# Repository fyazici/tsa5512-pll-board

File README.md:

# tsa5512-pll-board
PCB for VCO combined with the TV/VCR Tuner controller TSA5512T

VCO is implemented with a simple varactor controlled Colpitts oscillator. 
Capacitor/Inductor values should be adjusted according to the desired operating frequency range. Current component values are chosen to oscillate in FM band.
TSA5512 is a cheap Philips PLL IC mainly made for TV tuner applications. DIY-famous UV916 tuner also contains this chip (like many other tuners).
PLL is configured over I2C, which can easily be achieved with an Arduino board. Programming details can be found in the datasheet (http://pira.cz/pdf/TSA5512.pdf)

Some components are through-hole, because I've had a bunch of them at hand. SMD resistor/capacitors are spread all over the board and they can easily be found on any scrap electronic equipment with a sufficient size.
For higher frequency requirements (UHF band, ~300MHz) original tuner designs can be taken as a reference. BFR92 transistor will be more appropriate for the oscillator and special care should be taken in order to encapsulate the signal nets (t. lines and keepout regions mainly).

3D board view of the top-side:

Note that the gerber outputs are not up-to-date (belongs to an erroneus version). I've laser-printed the board so I did not care about special requirements of any PCB manufacturer. A revisit of layout is required to meet manufacturer demands (some I know of are: OSH Park, Seeedstudio)

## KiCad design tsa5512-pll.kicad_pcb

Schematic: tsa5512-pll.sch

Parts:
C1, C9, C14, C20: 10u; CP_Radial_D8.0mm_P3.80mm
C2, C10: 1u; CP_Radial_D5.0mm_P2.50mm
C3: 39n; C_1206_3216Metric_Pad1.24x1.80mm_HandSolder
C4, C12, C23: 4n7; C_1206_3216Metric_Pad1.24x1.80mm_HandSolder
C5: 180n; C_1206_3216Metric_Pad1.24x1.80mm_HandSolder
C6, C13, C24: 150p; C_1206_3216Metric_Pad1.24x1.80mm_HandSolder
C7, C8: 1n; C_1206_3216Metric_Pad1.24x1.80mm_HandSolder
C11: 27p; C_1206_3216Metric_Pad1.24x1.80mm_HandSolder
C15: 10n; C_1206_3216Metric_Pad1.24x1.80mm_HandSolder
C16, C17: 15p; C_1206_3216Metric_Pad1.24x1.80mm_HandSolder
C18: 330p; C_1206_3216Metric_Pad1.24x1.80mm_HandSolder
C19, C21: 47p; C_1206_3216Metric_Pad1.24x1.80mm_HandSolder
C22: 22p; C_1206_3216Metric_Pad1.24x1.80mm_HandSolder
D1, D2: BB221; D_DO-35_SOD27_P7.62mm_Horizontal
J1, J2, J3: Conn_01x04; PinHeader_1x04_P2.54mm_Vertical
L1: 100n; L_7.3x7.3_H3.5
Q1: BC848W; SOT-323_SC-70_Handsoldering
Q2: BF199; TO-92L_Inline_Wide
R1, R5, R6: 15k; R_1206_3216Metric_Pad1.24x1.80mm_HandSolder
R2, R3, R11: 10k; R_1206_3216Metric_Pad1.24x1.80mm_HandSolder
R4: 22k; R_1206_3216Metric_Pad1.24x1.80mm_HandSolder
R7: 270R; R_1206_3216Metric_Pad1.24x1.80mm_HandSolder
R8: 680R; R_1206_3216Metric_Pad1.24x1.80mm_HandSolder
R9, R10, R12: 4k7; R_1206_3216Metric_Pad1.24x1.80mm_HandSolder
TP1, TP2: Test_Point; TestPoint_Pad_D1.5mm
TP3: Test_Point; TestPoint_Pad_4.0x4.0mm
U1: L78L05_TO92; TO-92_Wide
U2: TSA5512T; SOIC-16W_5.3x10.2mm_P1.27mm
Y1: 4MHz; Crystal_HC49-4H_Vertical

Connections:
+5V: C9.1, C10.1, C12.1, C13.1, R2.1, R3.1, U1.1 (VO), U2.12
+12V: C1.1, C2.1, C4.1, C6.1, C23.1, C24.1, J1.1, J1.2, L1.1, R1.2, R5.1, U1.3 (VI)
/OSC_OUT: C7.1, R8.2
/SCL: J2.3, R3.2, U2.5
/SDA: J2.4, R2.2, U2.4
/VTUNE: C3.2, C21.1, Q1.3 (C), R1.1, R4.2, R11.1
GND: C1.2, C2.2, C4.2, C6.2, C8.2, C9.2, C10.2, C12.2, C13.2, C14.2, C15.2, C17.2, C19.2, C21.2, C23.2, C24.2, D2.2, J1.3, J1.4, J2.1, J2.2, J3.3, J3.4, Q1.2 (E), R6.2, R7.2, R9.2, R12.1, U1.2 (GND), U2.15
unnamed: C3.1, C5.2, R4.1
unnamed: C5.1, U2.1
unnamed: C7.2, U2.13
unnamed: C8.1, U2.14
unnamed: C11.1, U2.2
unnamed: C11.2, Y1.2
unnamed: C14.1, C15.1, Q2.3, R5.2, R6.1
unnamed: C16.1, C18.2, L1.2, Q2.1
unnamed: C16.2, C17.1, C22.1, Q2.2, R7.1, R8.1
unnamed: C18.1, D1.2, R9.1
unnamed: C19.1, C20.1, R10.1
unnamed: C20.2, J3.1, J3.2, R12.2
unnamed: C22.2, TP3.1
unnamed: D1.1, D2.1, R10.2, R11.2
unnamed: Q1.1 (B), U2.16
unnamed: TP1.1, U2.7
unnamed: TP2.1, U2.6
unnamed: U2.3, Y1.1

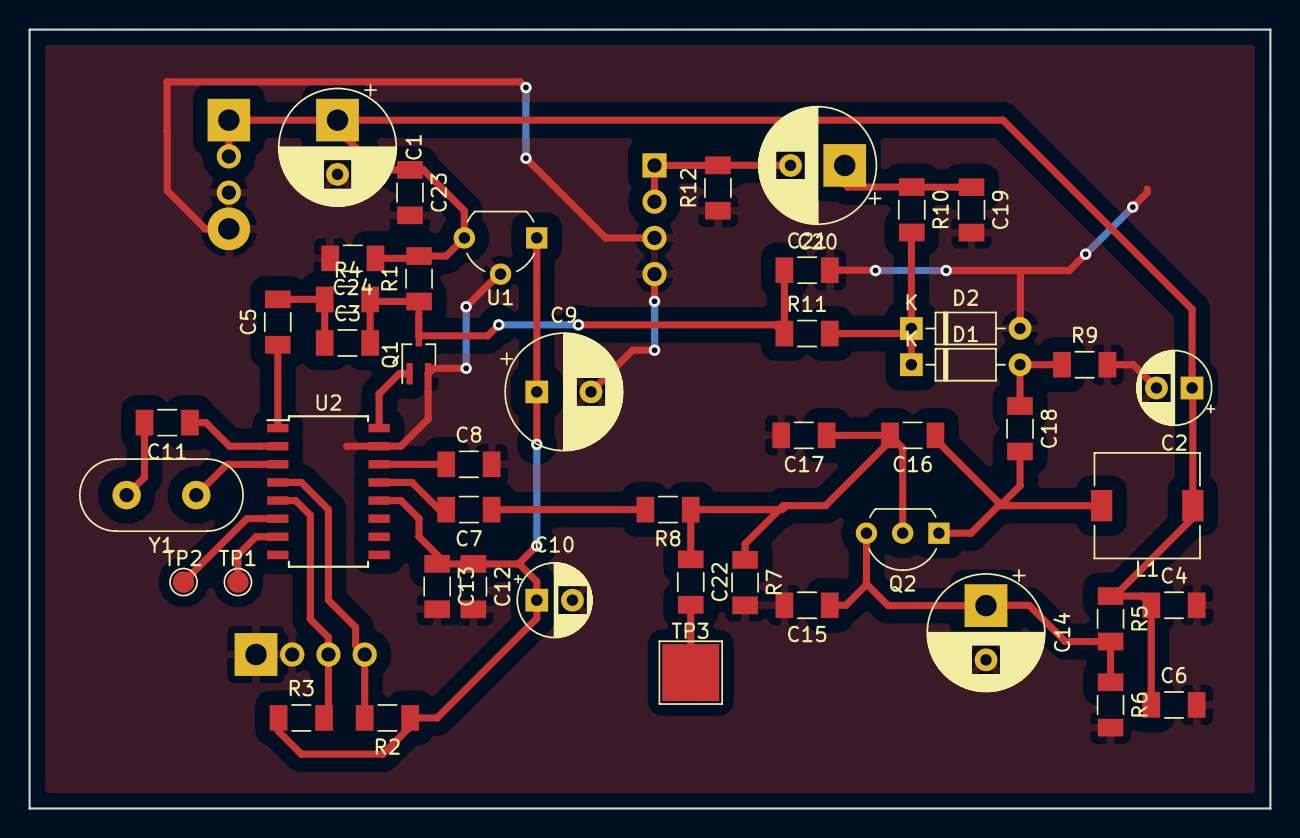
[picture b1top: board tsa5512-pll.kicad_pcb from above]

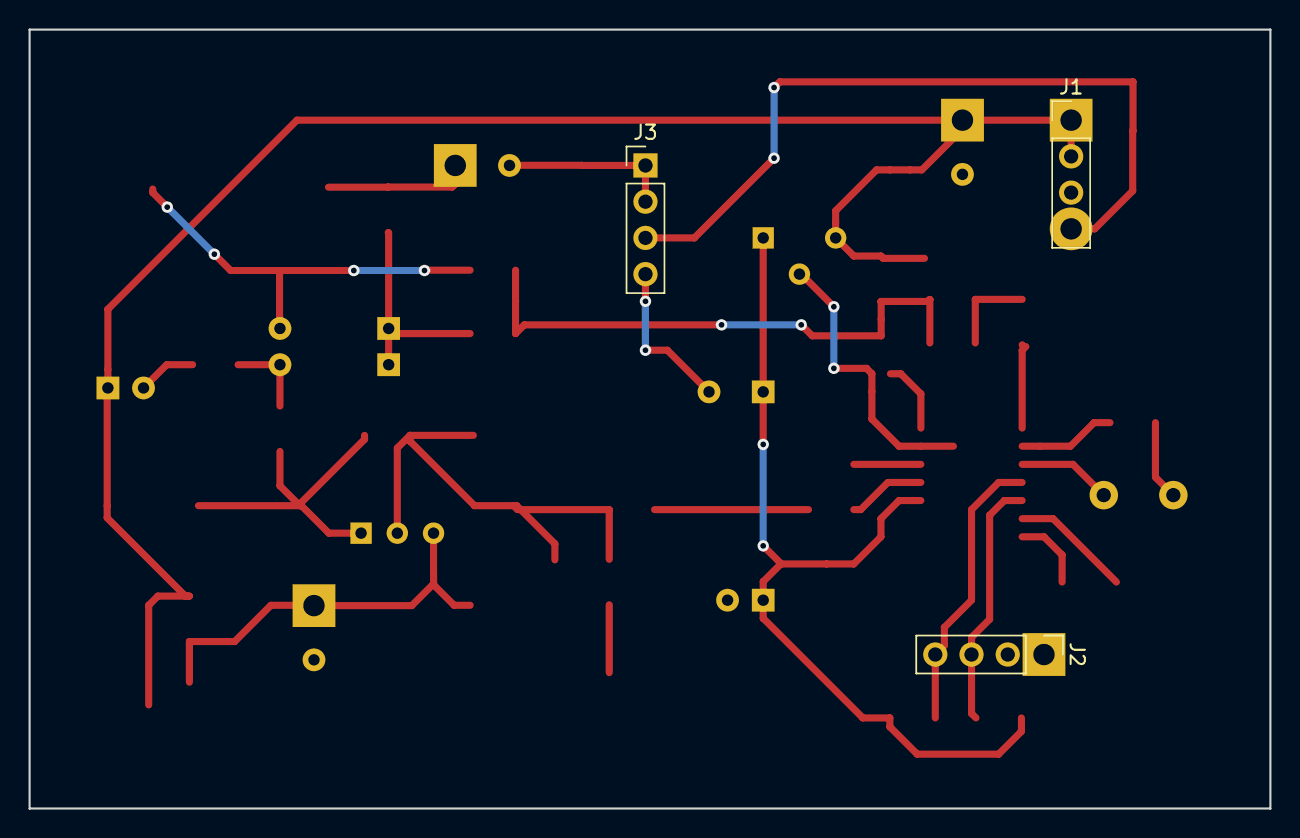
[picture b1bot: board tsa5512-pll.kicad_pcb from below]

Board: 2 copper layers, 87.0 x 54.6 mm, 50 parts (3 on the bottom side), 25 nets.
